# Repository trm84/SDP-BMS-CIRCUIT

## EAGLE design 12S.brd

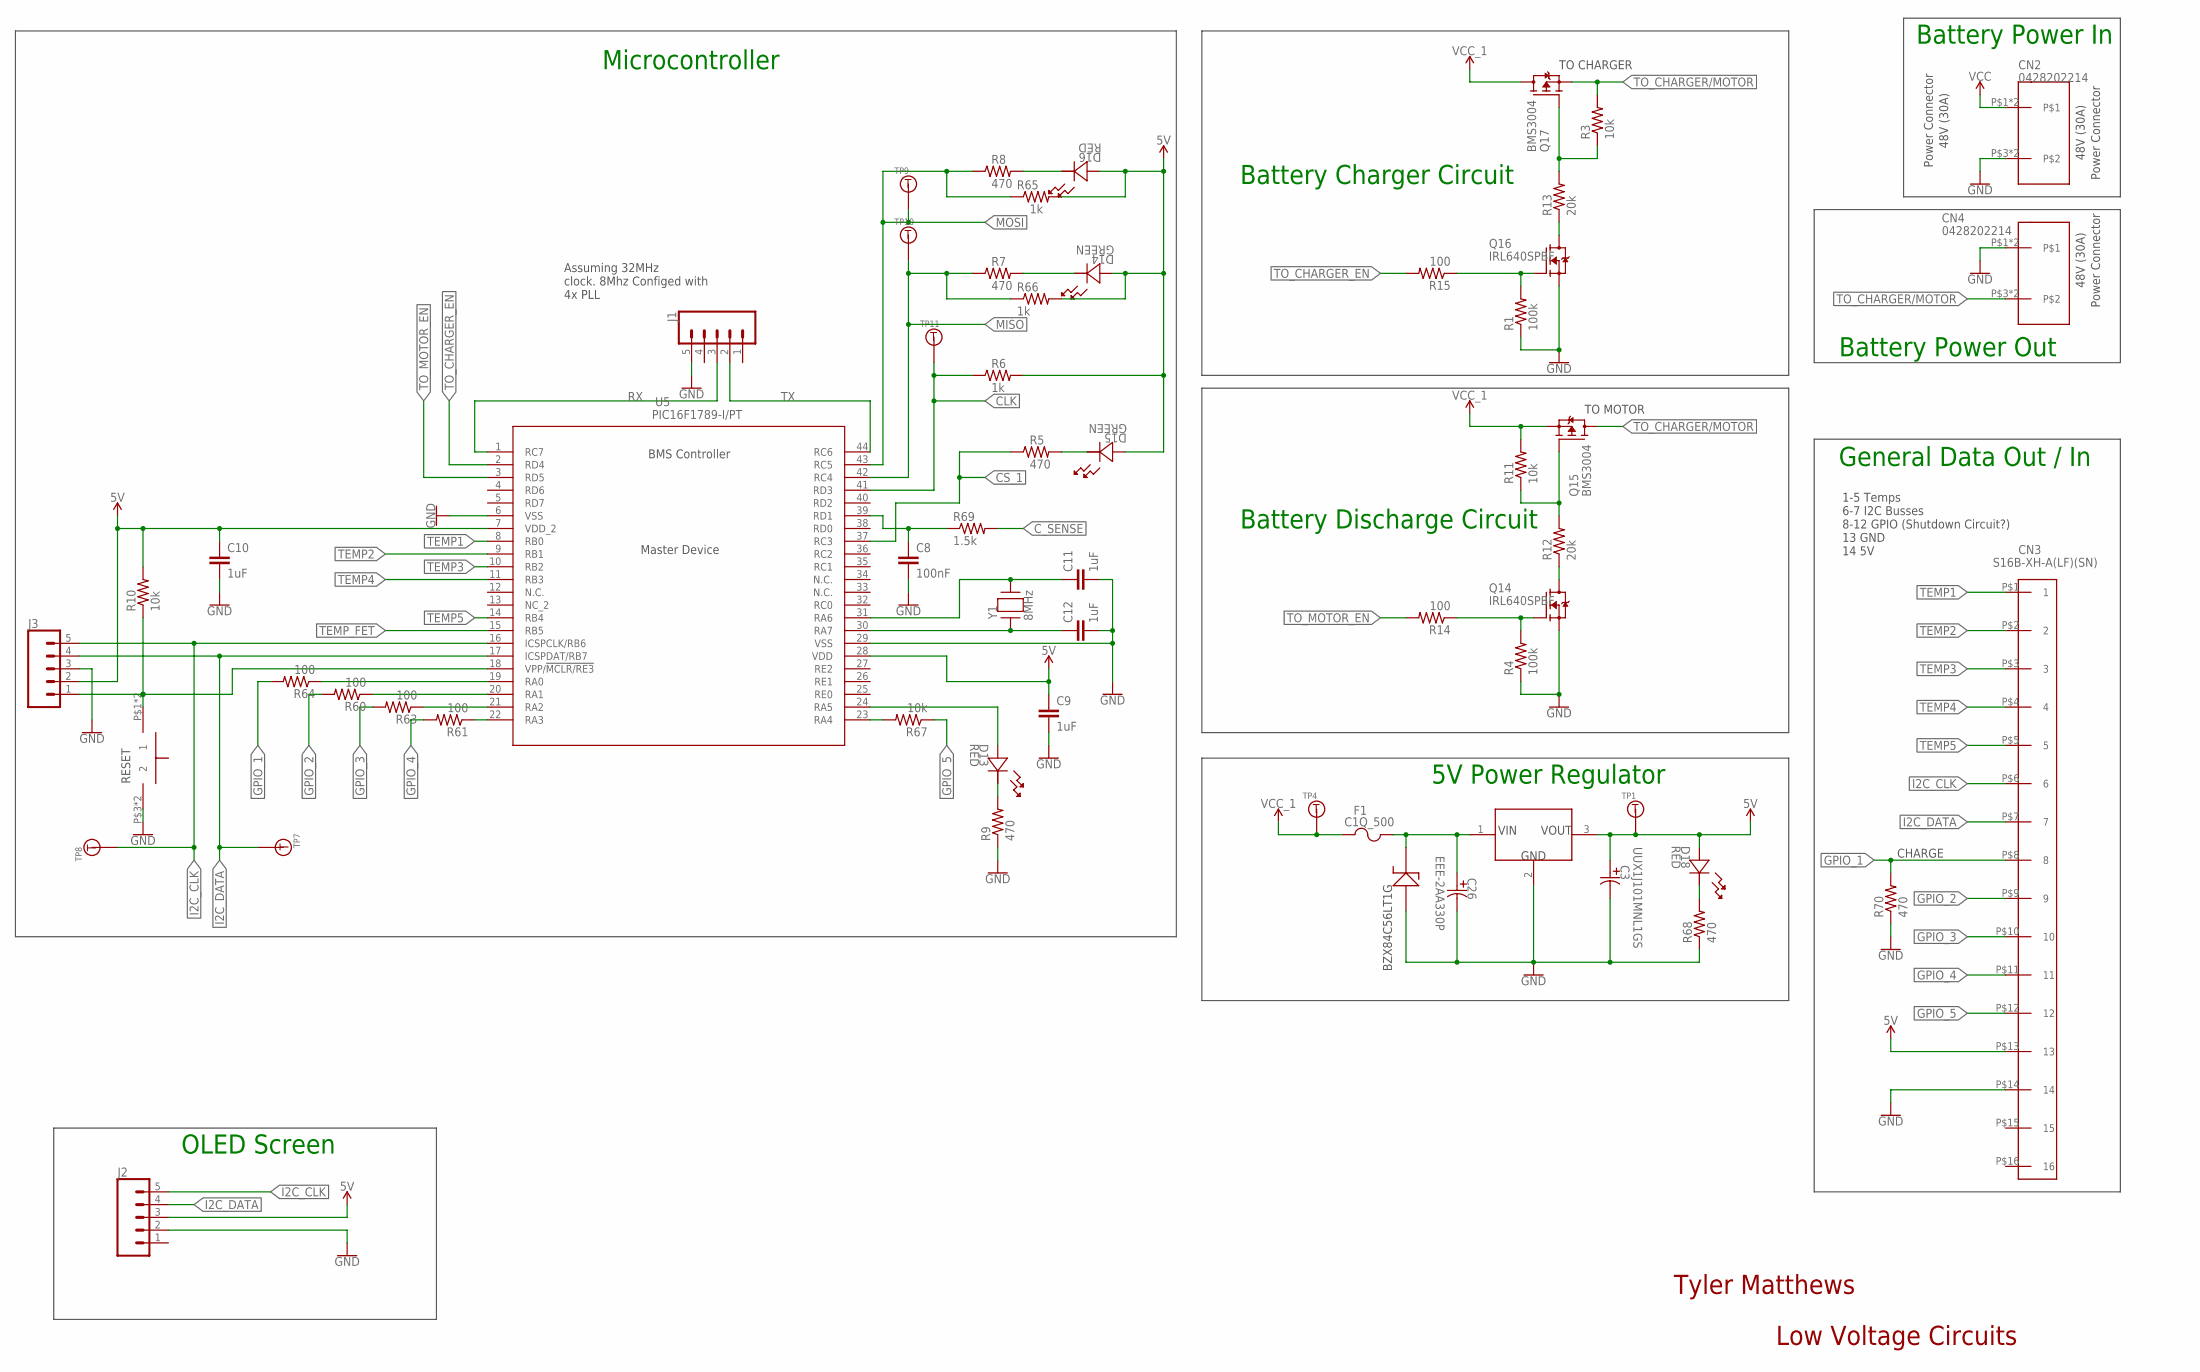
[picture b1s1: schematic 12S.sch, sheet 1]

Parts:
C3: UUX1J101MNL1GS; PCAP_10X10-ELECT
C8: 100nF; C0603
C9, C10, C11, C12: 1uF; C0603
C26: EEE-2AA330P; CAP_EEE_G
CN2, CN4: 0428202214
CN3: S16B-XH-A(LF)(SN)
D13, D16, D18: RED; LED_DIALIGHT_598
D14, D15: GREEN; LED_DIALIGHT_598
D17: BZX84C56LT1G; SOT-23
F1: C1Q_500; C1
J1, J2, J3: CONN_05; 1X05
Q14, Q16: IRL640SPBF; D2PAK
Q15, Q17: BMS3004; TO-220
R1, R4: 100k; R0603
R3, R10, R11, R67: 10k; R0603
R5, R7, R8, R9, R68, R70: 470; R0603
R6, R65, R66: 1k; R0603
R12, R13: 20k; R0603
R14, R15, R60, R61, R63, R64: 100; R0603
R69: 1.5k; R0603
S2: TL3305AF260QG
TP1, TP4, TP7, TP8, TP9, TP10, TP11: TP5015
U3: SRH05S05; SIP3
U5: PIC16F1789-I/PT; TQFP44_MC
Y1: 8MHz; CRYSTAL_HC49SDLF

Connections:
5V: C3.1 (11), C9.1, C10.1, CN3.P$13 (13), D14.2 (22), D15.2 (22), D16.2 (22), D18.2 (22), J2.3, J3.2, R6.2, R10.2, R65.2, R66.2, TP1.P$1, U3.3 (VOUT), U5.7 (VDD_2), U5.28 (VDD); also elsewhere on the board
CLK: R6.1, TP11.P$1, U5.41 (RD3); also elsewhere on the board
CS_1: R5.1, U5.37 (RC3); also elsewhere on the board
C_SENSE: R69.2; also elsewhere on the board
GND: C3.2 (22), C8.2, C9.2, C10.2, C11.2, C12.2, C26.2 (22), CN2.P$3, CN2.P$4, CN3.P$14 (14), CN4.P$1, CN4.P$2, D17.1, J1.5, J2.2, J3.3, Q14.2 (S), Q16.2 (S), R1.1, R4.1, R9.1, R68.1, R70.1, S2.P$3 (2), S2.P$4 (2), U3.2 (GND), U5.6 (VSS), U5.29 (VSS); also elsewhere on the board
GPIO_1: CN3.P$8 (8), R64.2, R70.2
GPIO_2: CN3.P$9 (9), R60.2
GPIO_3: CN3.P$10 (10), R63.2
GPIO_4: CN3.P$11 (11), R61.2
GPIO_5: CN3.P$12 (12), R67.1
I2C_CLK: CN3.P$6 (6), J2.5, J3.5, TP8.P$1, U5.16 (ICSPCLK/RB6)
I2C_DATA: CN3.P$7 (7), J2.4, J3.4, TP7.P$1, U5.17 (ICSPDAT/RB7)
MISO: R7.1, R66.1, TP10.P$1, U5.42 (RC4); also elsewhere on the board
MOSI: R8.1, R65.1, TP9.P$1, U5.43 (RC5); also elsewhere on the board
unnamed: D16.1 (11), R8.2
unnamed: D14.1 (11), R7.2
unnamed: D15.1 (11), R5.2
unnamed: Q17.1 (G), R3.1, R13.2
unnamed: R61.1, U5.22 (RA3)
unnamed: R63.1, U5.21 (RA2)
unnamed: R60.1, U5.20 (RA1)
unnamed: R64.1, U5.19 (RA0)
unnamed: D18.1 (11), R68.2
unnamed: R67.2, U5.23 (RA4)
unnamed: C8.1, R69.1, U5.39 (RD1)
unnamed: C26.1 (11), D17.3, F1.2, U3.1 (VIN)
unnamed: Q14.3 (D), R12.1
unnamed: C11.1, U5.31 (RA6), Y1.2
unnamed: C12.1, U5.30 (RA7), Y1.1
unnamed: Q15.1 (G), R11.1, R12.2
unnamed: Q14.1 (G), R4.2, R14.1
unnamed: Q16.3 (D), R13.1
unnamed: Q16.1 (G), R1.2, R15.1
unnamed: J3.1, R10.1, S2.P$1 (1), S2.P$2 (1), U5.18 (VPP/!MCLR/RE3)
unnamed: D13.2 (22), U5.24 (RA5)
unnamed: D13.1 (11), R9.2
RX: J1.3, U5.1 (RC7)
TEMP1: CN3.P$1 (1), U5.8 (RB0); also elsewhere on the board
TEMP2: CN3.P$2 (2), U5.9 (RB1); also elsewhere on the board
TEMP3: CN3.P$3 (3), U5.10 (RB2); also elsewhere on the board
TEMP4: CN3.P$4 (4), U5.11 (RB3); also elsewhere on the board
TEMP5: CN3.P$5 (5), U5.14 (RB4); also elsewhere on the board
TEMP_FET: U5.15 (RB5); also elsewhere on the board
TO_CHARGER/MOTOR: CN4.P$3, CN4.P$4, Q15.2 (D), Q17.3 (S), R3.2
TO_CHARGER_EN: R15.2, U5.2 (RD4)
TO_MOTOR_EN: R14.2, U5.3 (RD5)
TX: J1.2, U5.44 (RC6)
VCC: CN2.P$1, CN2.P$2; also elsewhere on the board
VCC_1: F1.1, Q15.3 (S), Q17.2 (D), R11.2, TP4.P$1; also elsewhere on the board

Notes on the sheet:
Master Device
BMS Controller
Assuming 32MHz clock. 8Mhz Configed with 4x PLL
Microcontroller
5V Power Regulator
Battery Discharge Circuit
Battery Charger Circuit
Power Connector
48V (30A)
Battery Power Out
General Data Out / In
1-5 Temps 6-7 I2C Busses 8-12 GPIO (Shutdown Circuit?) 13 GND 14 5V
Battery Power In
TO CHARGER
TO MOTOR
Tyler Matthews
Low Voltage Circuits
RESET
BZX84C56LT1G
CHARGE
OLED Screen

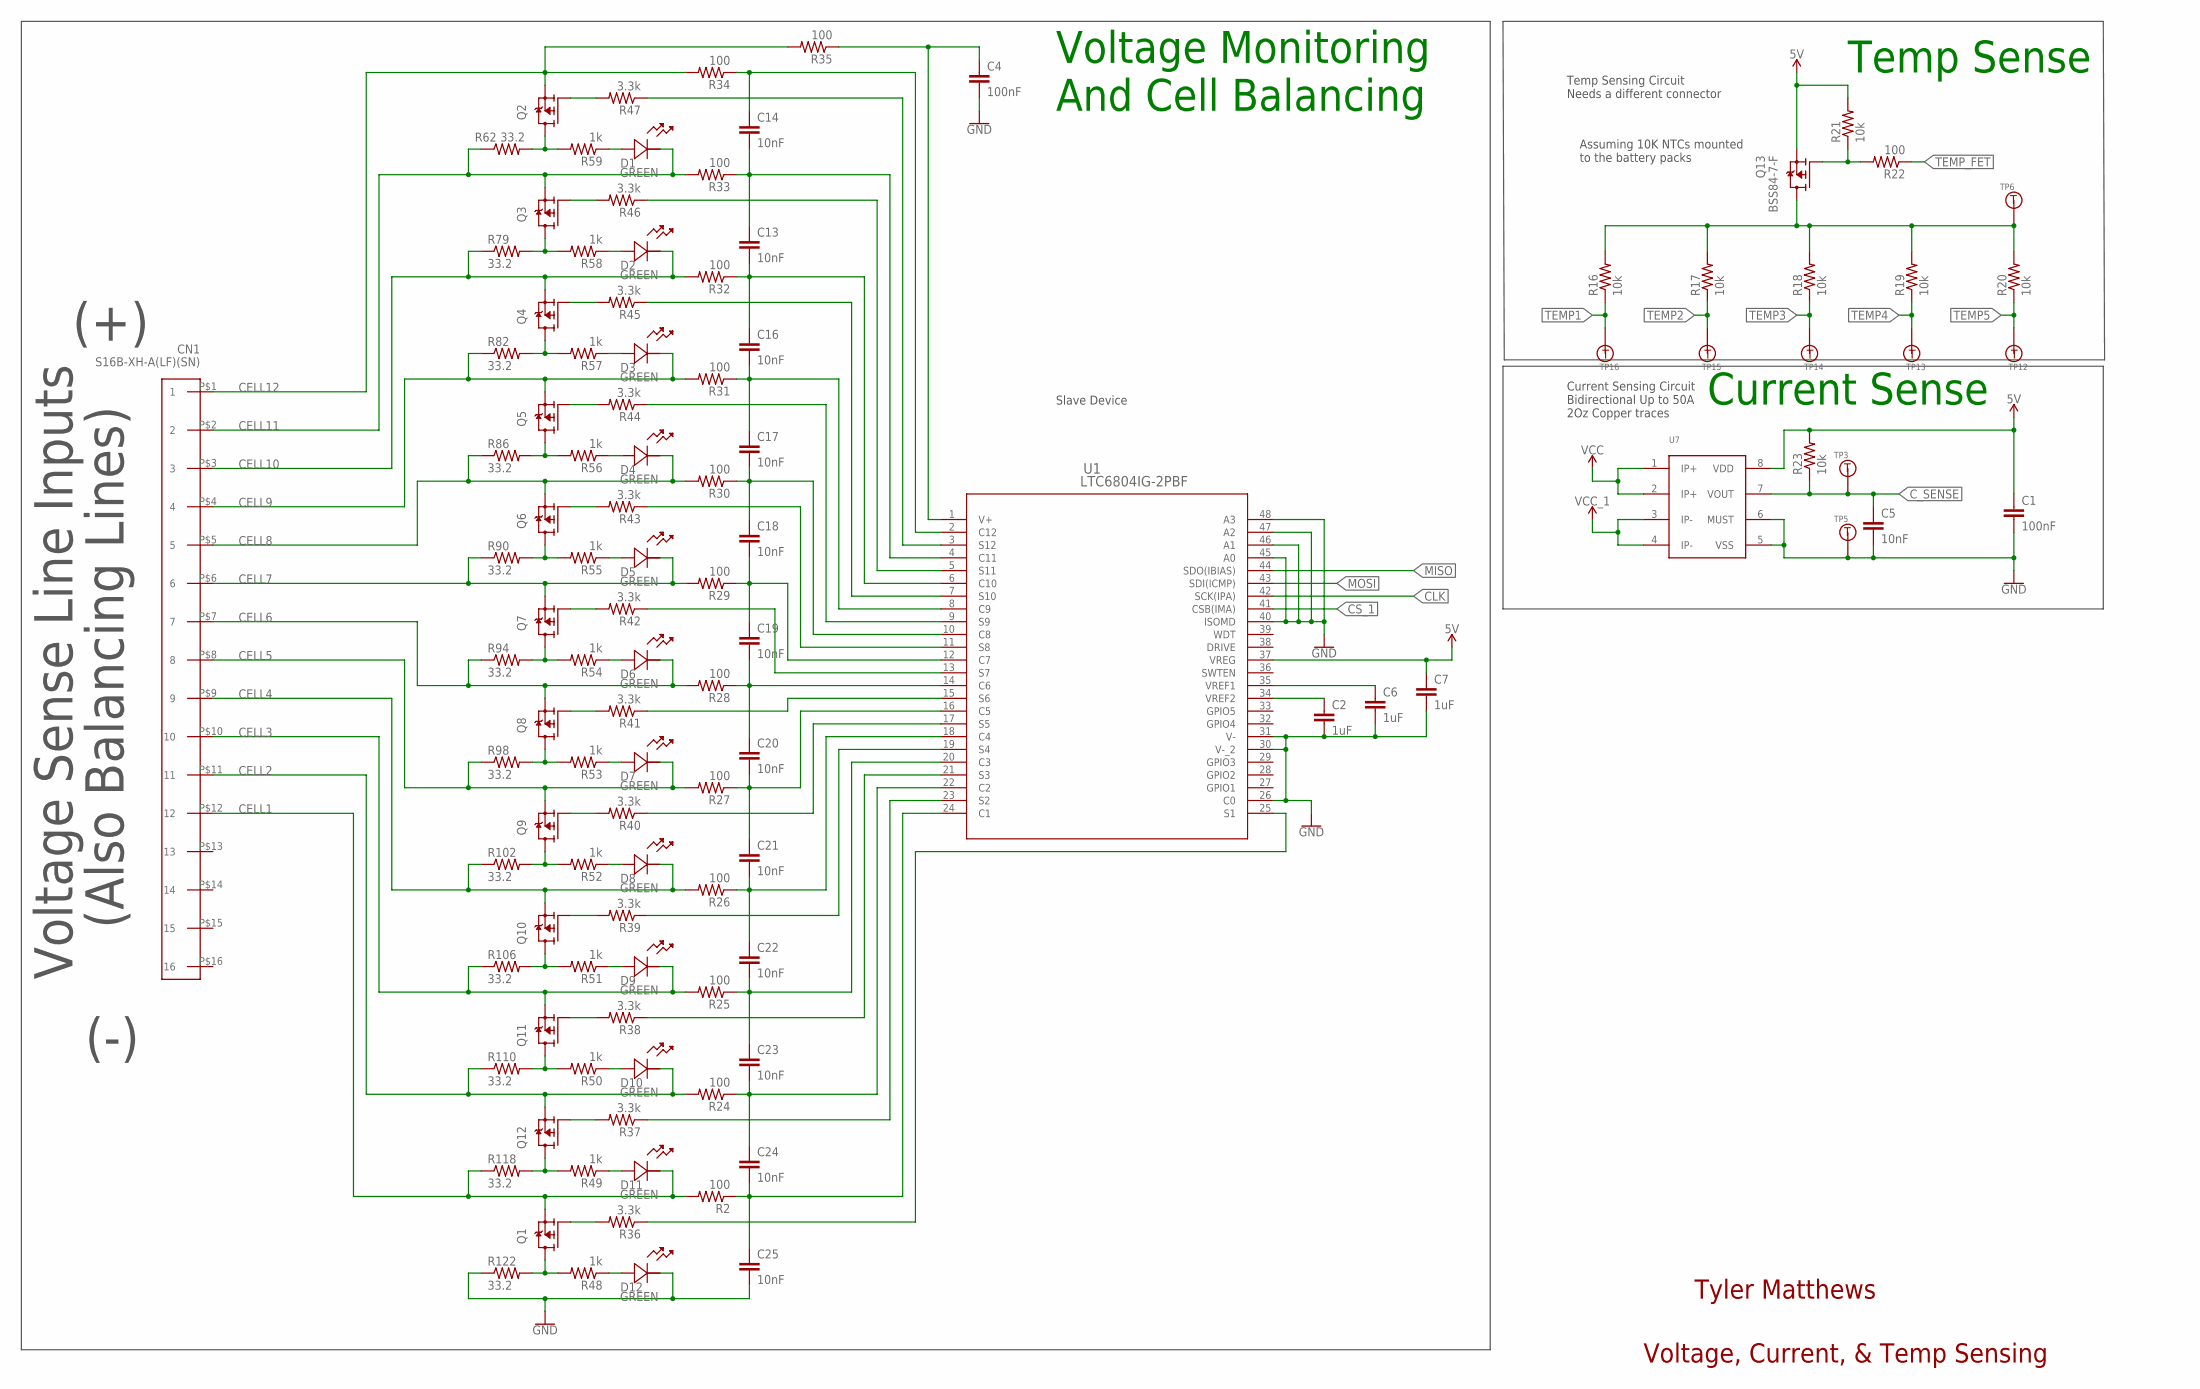
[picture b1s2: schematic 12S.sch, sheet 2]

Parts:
C1, C4: 100nF; C0603
C2, C6, C7: 1uF; C0603
C5, C13, C14, C16, C17, C18, C19, C20, C21, C22, C23, C24, C25: 10nF; C0603
CN1: S16B-XH-A(LF)(SN)
D1, D2, D3, D4, D5, D6, D7, D8, D9, D10, D11, D12: GREEN; LED_DIALIGHT_598
Q1, Q2, Q3, Q4, Q5, Q6, Q7, Q8, Q9, Q10, Q11, Q12: BSS308PEH6327XTSA1
Q13: BSS84-7-F; SOT-23
R2, R22, R24, R25, R26, R27, R28, R29, R30, R31, R32, R33, R34, R35: 100; R0603
R16, R17, R18, R19, R20, R21, R23: 10k; R0603
R36, R37, R38, R39, R40, R41, R42, R43, R44, R45, R46, R47: 3.3k; R0603
R48, R49, R50, R51, R52, R53, R54, R55, R56, R57, R58, R59: 1k; R0603
R62, R79, R82, R86, R90, R94, R98, R102, R106, R110, R118, R122: 33.2; R0805
TP3, TP5, TP6, TP12, TP13, TP14, TP15, TP16: TP5015
U1: LTC6804IG-2PBF; SSOP-48_G
U7: MLX91210; SOIC-8

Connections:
5V: C1.1, C7.1, Q13.2 (S), R21.2, R23.2, U1.37 (VREG), U7.8 (VDD); also elsewhere on the board
CELL1: CN1.P$12 (12), D11.1 (11), Q1.P$S (S), R2.2, R118.1
CELL2: CN1.P$11 (11), D10.1 (11), Q12.P$S (S), R24.2, R110.1
CELL3: CN1.P$10 (10), D9.1 (11), Q11.P$S (S), R25.2, R106.1
CELL4: CN1.P$9 (9), D8.1 (11), Q10.P$S (S), R26.2, R102.1
CELL5: CN1.P$8 (8), D7.1 (11), Q9.P$S (S), R27.2, R98.1
CELL6: CN1.P$7 (7), D6.1 (11), Q8.P$S (S), R28.2, R94.1
CELL7: CN1.P$6 (6), D5.1 (11), Q7.P$S (S), R29.2, R90.1
CELL8: CN1.P$5 (5), D4.1 (11), Q6.P$S (S), R30.2, R86.1
CELL9: CN1.P$4 (4), D3.1 (11), Q5.P$S (S), R31.2, R82.1
CELL10: CN1.P$3 (3), D2.1 (11), Q4.P$S (S), R32.2, R79.1
CELL11: CN1.P$2 (2), D1.1 (11), Q3.P$S (S), R33.2, R62.1
CELL12: CN1.P$1 (1), Q2.P$S (S), R34.2, R35.2
CLK: U1.42 (SCK(IPA)); also elsewhere on the board
CS_1: U1.41 (CSB(IMA)); also elsewhere on the board
C_SENSE: C5.1, R23.1, TP3.P$1, U7.7 (VOUT); also elsewhere on the board
GND: C1.2, C2.2, C4.2, C5.2, C6.2, C7.2, C25.2, D12.1 (11), R122.1, TP5.P$1, U1.26 (C0), U1.30 (V-_2), U1.31 (V-), U1.40 (ISOMD), U1.45 (A0), U1.46 (A1), U1.47 (A2), U1.48 (A3), U7.5 (VSS), U7.6 (MUST); also elsewhere on the board
MISO: U1.44 (SDO(IBIAS)); also elsewhere on the board
MOSI: U1.43 (SDI(ICMP)); also elsewhere on the board
unnamed: C6.1, U1.35 (VREF1)
unnamed: C2.1, U1.34 (VREF2)
unnamed: Q13.1 (G), R21.1, R22.2
unnamed: Q13.3 (D), R16.2, R17.2, R18.2, R19.2, R20.2, TP6.P$1
unnamed: Q2.P$G (G), R47.2
unnamed: R47.1, U1.3 (S12)
unnamed: C14.1, R34.1, U1.2 (C12)
unnamed: Q2.P$D (D), R59.2, R62.2
unnamed: D1.2 (22), R59.1
unnamed: C13.1, C14.2, R33.1, U1.4 (C11)
unnamed: R46.1, U1.5 (S11)
unnamed: Q3.P$G (G), R46.2
unnamed: Q3.P$D (D), R58.2, R79.2
unnamed: D2.2 (22), R58.1
unnamed: C13.2, C16.1, R32.1, U1.6 (C10)
unnamed: Q4.P$G (G), R45.2
unnamed: R45.1, U1.7 (S10)
unnamed: Q4.P$D (D), R57.2, R82.2
unnamed: D3.2 (22), R57.1
unnamed: Q5.P$G (G), R44.2
unnamed: C16.2, C17.1, R31.1, U1.8 (C9)
unnamed: R44.1, U1.9 (S9)
unnamed: Q5.P$D (D), R56.2, R86.2
unnamed: D4.2 (22), R56.1
unnamed: C17.2, C18.1, R30.1, U1.10 (C8)
unnamed: Q6.P$G (G), R43.2
unnamed: R43.1, U1.11 (S8)
unnamed: Q6.P$D (D), R55.2, R90.2
unnamed: D5.2 (22), R55.1
unnamed: C18.2, C19.1, R29.1, U1.12 (C7)
unnamed: Q7.P$G (G), R42.2
unnamed: Q7.P$D (D), R54.2, R94.2
unnamed: D6.2 (22), R54.1
unnamed: Q8.P$G (G), R41.2
unnamed: Q8.P$D (D), R53.2, R98.2
unnamed: D7.2 (22), R53.1
unnamed: Q9.P$G (G), R40.2
unnamed: Q9.P$D (D), R52.2, R102.2
unnamed: D8.2 (22), R52.1
unnamed: Q10.P$G (G), R39.2
unnamed: Q10.P$D (D), R51.2, R106.2
unnamed: D9.2 (22), R51.1
unnamed: Q11.P$G (G), R38.2
unnamed: Q11.P$D (D), R50.2, R110.2
unnamed: D10.2 (22), R50.1
unnamed: C23.2, C24.1, R24.1, U1.22 (C2)
unnamed: R38.1, U1.21 (S3)
unnamed: C22.2, C23.1, R25.1, U1.20 (C3)
unnamed: R39.1, U1.19 (S4)
unnamed: C21.2, C22.1, R26.1, U1.18 (C4)
unnamed: R40.1, U1.17 (S5)
unnamed: C20.2, C21.1, R27.1, U1.16 (C5)
unnamed: R41.1, U1.15 (S6)
unnamed: C19.2, C20.1, R28.1, U1.14 (C6)
unnamed: R42.1, U1.13 (S7)
unnamed: Q12.P$G (G), R37.2
unnamed: Q12.P$D (D), R49.2, R118.2
unnamed: D11.2 (22), R49.1
unnamed: R37.1, U1.23 (S2)
unnamed: C24.2, C25.1, R2.1, U1.24 (C1)
unnamed: Q1.P$G (G), R36.2
unnamed: Q1.P$D (D), R48.2, R122.2
unnamed: D12.2 (22), R48.1
unnamed: R36.1, U1.25 (S1)
TEMP1: R16.1, TP16.P$1; also elsewhere on the board
TEMP2: R17.1, TP15.P$1; also elsewhere on the board
TEMP3: R18.1, TP14.P$1; also elsewhere on the board
TEMP4: R19.1, TP13.P$1; also elsewhere on the board
TEMP5: R20.1, TP12.P$1; also elsewhere on the board
TEMP_FET: R22.1; also elsewhere on the board
V+: C4.1, R35.1, U1.1 (V+)
VCC: U7.1 (IP+), U7.2 (IP+); also elsewhere on the board
VCC_1: U7.3 (IP-), U7.4 (IP-); also elsewhere on the board

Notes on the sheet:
Slave Device
Voltage Monitoring And Cell Balancing
Voltage Sense Line Inputs
(Also Balancing Lines)
(+)
(-)
Temp Sensing Circuit Needs a different connector
Assuming 10K NTCs mounted to the battery packs
Temp Sense
Current Sensing Circuit Bidirectional Up to 50A 2Oz Copper traces
Current Sense
Tyler Matthews
Voltage, Current, & Temp Sensing

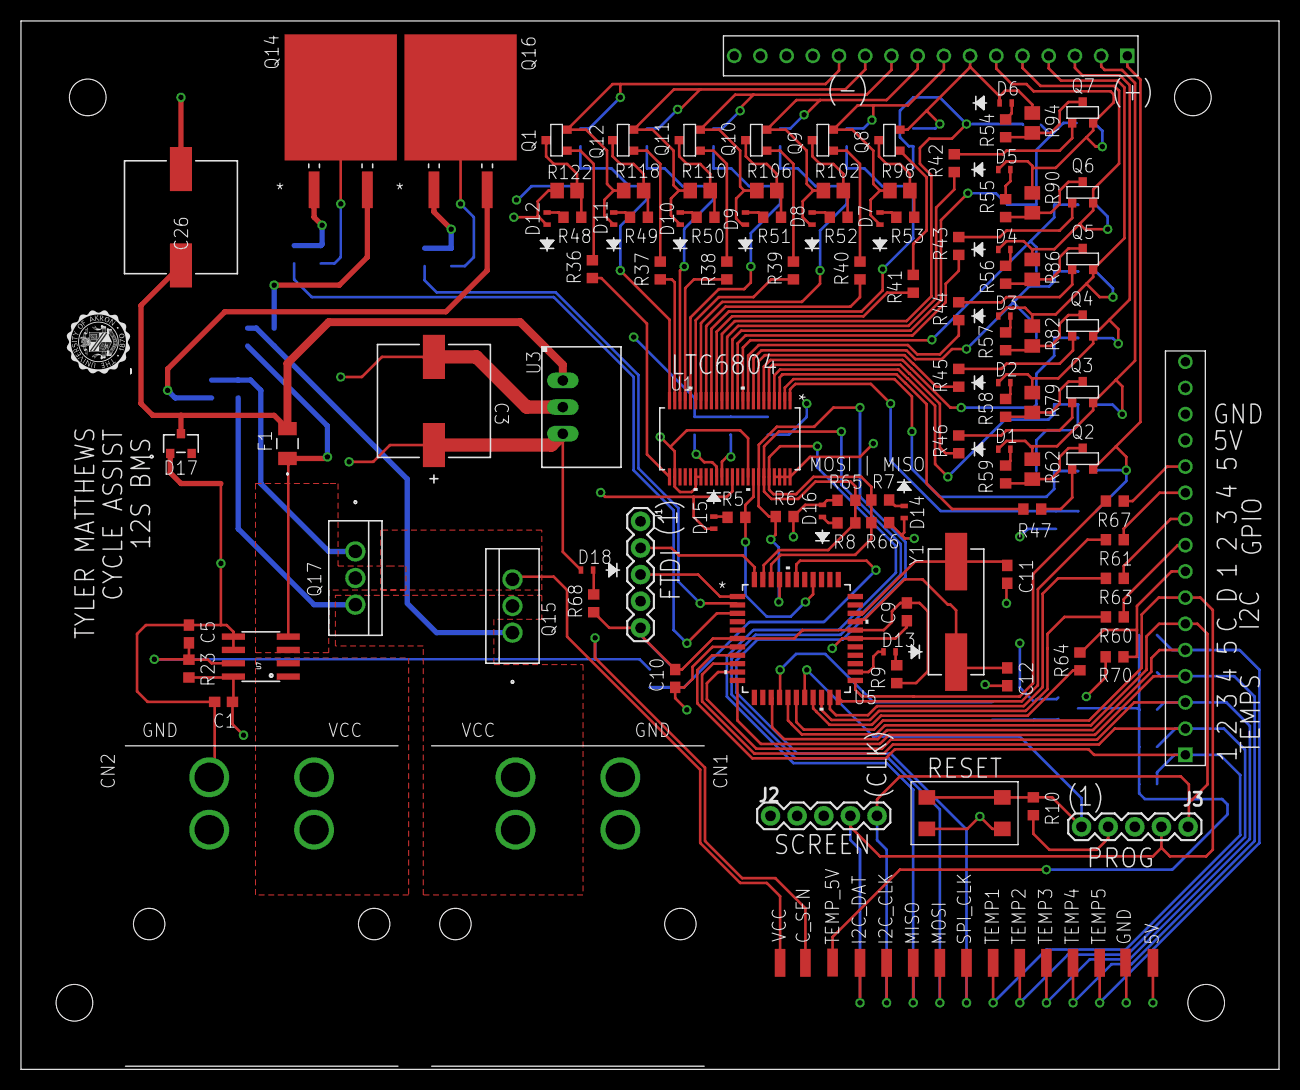
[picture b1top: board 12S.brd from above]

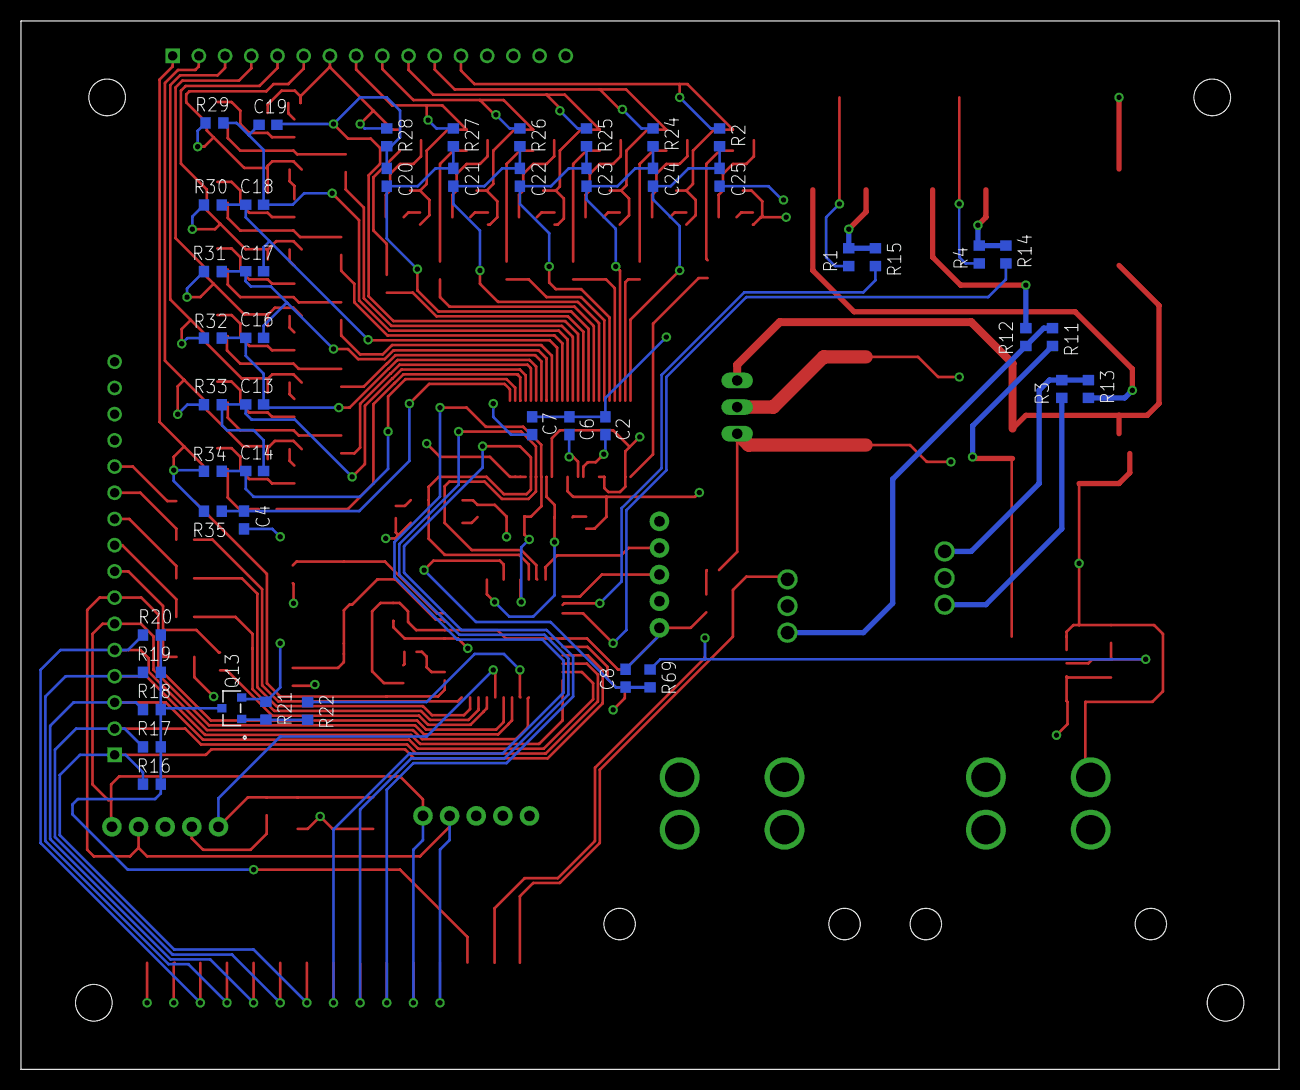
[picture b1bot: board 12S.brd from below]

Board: 4 copper layers, 120.0 x 100.0 mm, 170 parts (47 on the bottom side), 126 nets.

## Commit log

2019-02-24 second commit

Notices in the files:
parts and their libraries:
SparkFun-PowerSymbols: Licensing: Creative Commons ShareAlike 4.0 International - https://creativecommons.org/licenses/by-sa/4.0
